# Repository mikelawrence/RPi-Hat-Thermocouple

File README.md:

# Raspberry Pi Thermocouple Hat
This is a [Raspberry Pi B+ Hat](https://github.com/raspberrypi/hats) PCB that supports:
* Three MAX31855 Thermocouple Converters for remote temperature sensing
* DS18S20 1-Wire Thermometer for local hat temperature
* DS3231M I2C Real Time Clock for keeping the time when Raspberry is not connected to the internet
* Magnetic Buzzer/Alert (Added with Rev 1.1)

PCB is designed in [KiCad](http://kicad.org) which is a great free EDA toolset and is based on [RPi_Hat_Template](https://github.com/xesscorp/RPi_Hat_Template) by XESS Corp.

## Status
* Rev 1.2 PCB  has been ordered from OSH Park but has NOT been tested yet.
  * Added R7 to prevent the Alert Buzzer from sounding when powered on.
  * Added Analog Power LDO Regulator to help with noise on the MAX31855's temperature readings. Not clear if this will help.
  * You can order parts from Mouser using this [shared BOM](http://www.mouser.com/ProjectManager/ProjectDetail.aspx?AccessID=20F70B46A4).
  * You can order the PCB from OSH Park using this [link](https://oshpark.com/shared_projects/3POTkoNz).
* Rev 1.1 PCB added an Alert Buzzer and has been ordered from OSH Park, assembled, and tested.
  * The Alert Buzzer sounds as soon as the board is powered. Adding a pulldown to base of NUD3124 fixes the problem.
  * There is occasional noise in the temperature readings from the MAX31855's.
* Rev 1.0 PCB has been ordered from OSH Park, assembled, and tested. It is fully operational.

## Board Preview

## Raspberry Pi Setup
This setup makes two key assumptions. First you are using Raspbian Jessie. Second Python3 is the target programming environment. Python3 should be installed by default but if it isn't run `sudo apt-get install python3-dev`.

### Configure ID EEPROM
Raspberry Pi Hats require an ID EEPROM with data that uniquely identifies every hat ever made. Start by cloning this repository on your Raspberry Pi, building the EEPROM tools, and make the the `eeprom_settings.eep` file.
```
cd ~/Documents
git clone https://github.com/mikelawrence/RPi-Hat-Thermocouple
cd ~/Documents/RPi-Hat-Thermocouple/eeprom/
make all
./eepmake eeprom_settings.txt eeprom_settings.eep
```
The next command writes the freshly generated and unique `eeprom_settings.eep` file to the EEPROM but you must push and hold the write switch on the hat before executing this command. By default the EEPROM on the hat is write protected. Pushing the write switch allows writes to occur while the switch is pushed.
```
sudo ./eepflash.sh -w -f=eeprom_settings.eep -t=24c32
```
You will see the following if writing to the EEPROM was successful.
```
This will attempt to talk to an eeprom at i2c address 0x50. Make sure there is an eeprom at this address.
This script comes with ABSOLUTELY no warranty. Continue only if you know what you are doing.
Do you wish to continue? (yes/no): yes
Writing...
0+1 records in
0+1 records out
117 bytes (117 B) copied, 2.31931 s, 0.1 kB/s
Done.
```
This is what you will see if there is a problem communicating with the EEPROM.
```
This will attempt to talk to an eeprom at i2c address 0x50. Make sure there is an eeprom at this address.
This script comes with ABSOLUTELY no warranty. Continue only if you know what you are doing.
Do you wish to continue? (yes/no): yes
Writing...
dd: error writing ‘/sys/class/i2c-adapter/i2c-3/3-0050/eeprom’: Connection timed out
0+1 records in
0+0 records out
0 bytes (0 B) copied, 0.0539977 s, 0.0 kB/s
Error doing I/O operation.
```
If you succesfuly wrote the EEPROM there is nothing else left to do here.

### Setup Interfaces
For this Hat you will need to enable the SPI, I2C and 1-Wire interfaces. From the command line type
`sudo raspi-config ` and follow the prompts to install SPI support in the kernel.

Now follow the same actions but enabling the I2C and 1-Wire interfaces.

It's time to reboot your Raspberry Pi with `sudo reboot`.

### Configuring the DS3231 RTC
Now let's see if the RTC is is present on the I2C bus by running `sudo i2cdetect -y 1`. If you get a `command not found` you will need to install it with `sudo apt-get install python-smbus i2c-tools`. Looking at the output of the `i2cdetect` command you will see `68` in a field of `--` when the RTC is detected on the bus.
```
pi@raspberrypi:~ $ sudo i2cdetect -y 1
     0  1  2  3  4  5  6  7  8  9  a  b  c  d  e  f
00:          -- -- -- -- -- -- -- -- -- -- -- -- --
10: -- -- -- -- -- -- -- -- -- -- -- -- -- -- -- --
20: -- -- -- -- -- -- -- -- -- -- -- -- -- -- -- --
30: -- -- -- -- -- -- -- -- -- -- -- -- -- -- -- --
40: -- -- -- -- -- -- -- -- -- -- -- -- -- -- -- --
50: -- -- -- -- -- -- -- -- -- -- -- -- -- -- -- --
60: -- -- -- -- -- -- -- -- 68 -- -- -- -- -- -- --
70: -- -- -- -- -- -- -- --                         
```
Enable kernel support for the DS3231 RTC by adding a device tree overlay by running `sudo nano /boot/config.txt` and adding the following to the end of the file. Don't forget to save the file.
```
# Enable Real Time Clock
dtoverlay=i2c-rtc,ds3231
```
Reboot again. Now when `sudo i2cdetect -y 1` is run we see:
```
pi@raspberrypi:~ $ sudo i2cdetect -y 1
     0  1  2  3  4  5  6  7  8  9  a  b  c  d  e  f
00:          -- -- -- -- -- -- -- -- -- -- -- -- --
10: -- -- -- -- -- -- -- -- -- -- -- -- -- -- -- --
20: -- -- -- -- -- -- -- -- -- -- -- -- -- -- -- --
30: -- -- -- -- -- -- -- -- -- -- -- -- -- -- -- --
40: -- -- -- -- -- -- -- -- -- -- -- -- -- -- -- --
50: -- -- -- -- -- -- -- -- -- -- -- -- -- -- -- --
60: -- -- -- -- -- -- -- -- UU -- -- -- -- -- -- --
70: -- -- -- -- -- -- -- --                         
```
The `UU` at address 68 means the RTC is currently in use by a driver or in other words we have success! Now disable the fake hwclock because it will interfere with our new RTC. Issue the following commands.
```
sudo apt-get -y remove fake-hwclock
sudo update-rc.d -f fake-hwclock remove
```
Next run `sudo nano /lib/udev/hwclock-set` and comment out the following lines. This puts the original clock script back to normal.
```
#if [ -e /run/systemd/system ] ; then
# exit 0
#fi
```
### Setting the time in the RTC
First make sure you have installed the CR1225 battery on the Hat. Next verify the Raspberry Pi has the correct time by typing `date`.
```
pi@raspberrypi:~ $ date
Fri Mar 10 16:52:48 CST 2017
```
If the time is not correct connect the Raspberry Pi to a network via Ethernet or WiFi and allow it synchronize with Internet time servers or set the time manually. Once the time is correct issue this command `sudo hwclock -w`. This will set the RTC time to current system time. The next time the Raspberry Pi is booted it will get it's time from the RTC.

### Using the DS18S20 1-Wire Thermometer
[Here](https://github.com/timofurrer/w1thermsensor) is a nice 1-Wire python library that also supports command line reading of the temperature. If you get a 'command not found' then install it with `sudo apt-get install python3-w1thermsensor`.

Now test the Thermocouple Hat's DS18S20 temperature sensor with `pi@raspberrypi:~ $`.
```
pi@raspberrypi:~ $ w1thermsensor all
Got temperatures of 1 sensors:
  Sensor 1 (0008033f727f) measured temperature: 32.312 celsius
```
### Using the MAX31855 SPI Thermocouple Converters
The Thermocouple Hat design gets around the Raspberry Pi limitation of only two chip enables for the hardware SPI0 interface by adding a 74LVC139A 2to4 Decoder to CEO. The address lines of the 2to4 decoder are connected to GPIO24 and GPIO23 so when SPI0.CE0 is sent low only one of the Thermocouple converters will be selected according to the following logic.

| GPIO23 (Pin 16) | GPIO24 (Pin 18) | Thermocouple |
|:---------------:|:---------------:|--------------|
|        0        |        0        | TC1          |
|        0        |        1        | TC2          |
|        1        |        0        | TC3          |
|        1        |        1        | Invalid      |

[Spidev](https://github.com/doceme/py-spidev) is a commonly used Python library for Raspberry Pi SPI programming. This library is most likely already installed but if not install it with `sudo apt-get install python3-spidev`. Assuming you already cloned this repository issue this command `~/Documents/RPi-Hat-Thermocouple/code/test.py` to see the DS18S20 PCB and thermocouple temperatures. Note when I ran the test on my board there was only one connected thermocouple so the other MAX31855K's show as 'No thermocouple connected'.
```
pi@raspberrypi:~ $ ~/Documents/RPi-Hat-Thermocouple/code/test.py
Press Ctrl-C to quit.
Testing alert buzzer...

DS18S20 on PCB: 28.88C / 83.97F
Thermocouple 0: 21.63C / 70.93F
Thermocouple 1: Error - No thermocouple connected
Thermocouple 2: Error - No thermocouple connected
```
# Acknowledgments
[Adafruit](www.adafruit.com) released a guide to [configuring a RTC on a Raspberry Pi](https://cdn-learn.adafruit.com/downloads/pdf/adding-a-real-time-clock-to-raspberry-pi.pdf) that was extremely helpful is setting up the DS3231M RTC. The MAX31855 code is based on an Adafruit [library](https://github.com/adafruit/Adafruit_Python_MAX31855).

Adafruit has breakout boards for the key chips on this Hat here: [RTC](https://www.adafruit.com/products/3013) and [MAX31855](https://www.adafruit.com/products/269). They support the open soruce/hardware community so support them.

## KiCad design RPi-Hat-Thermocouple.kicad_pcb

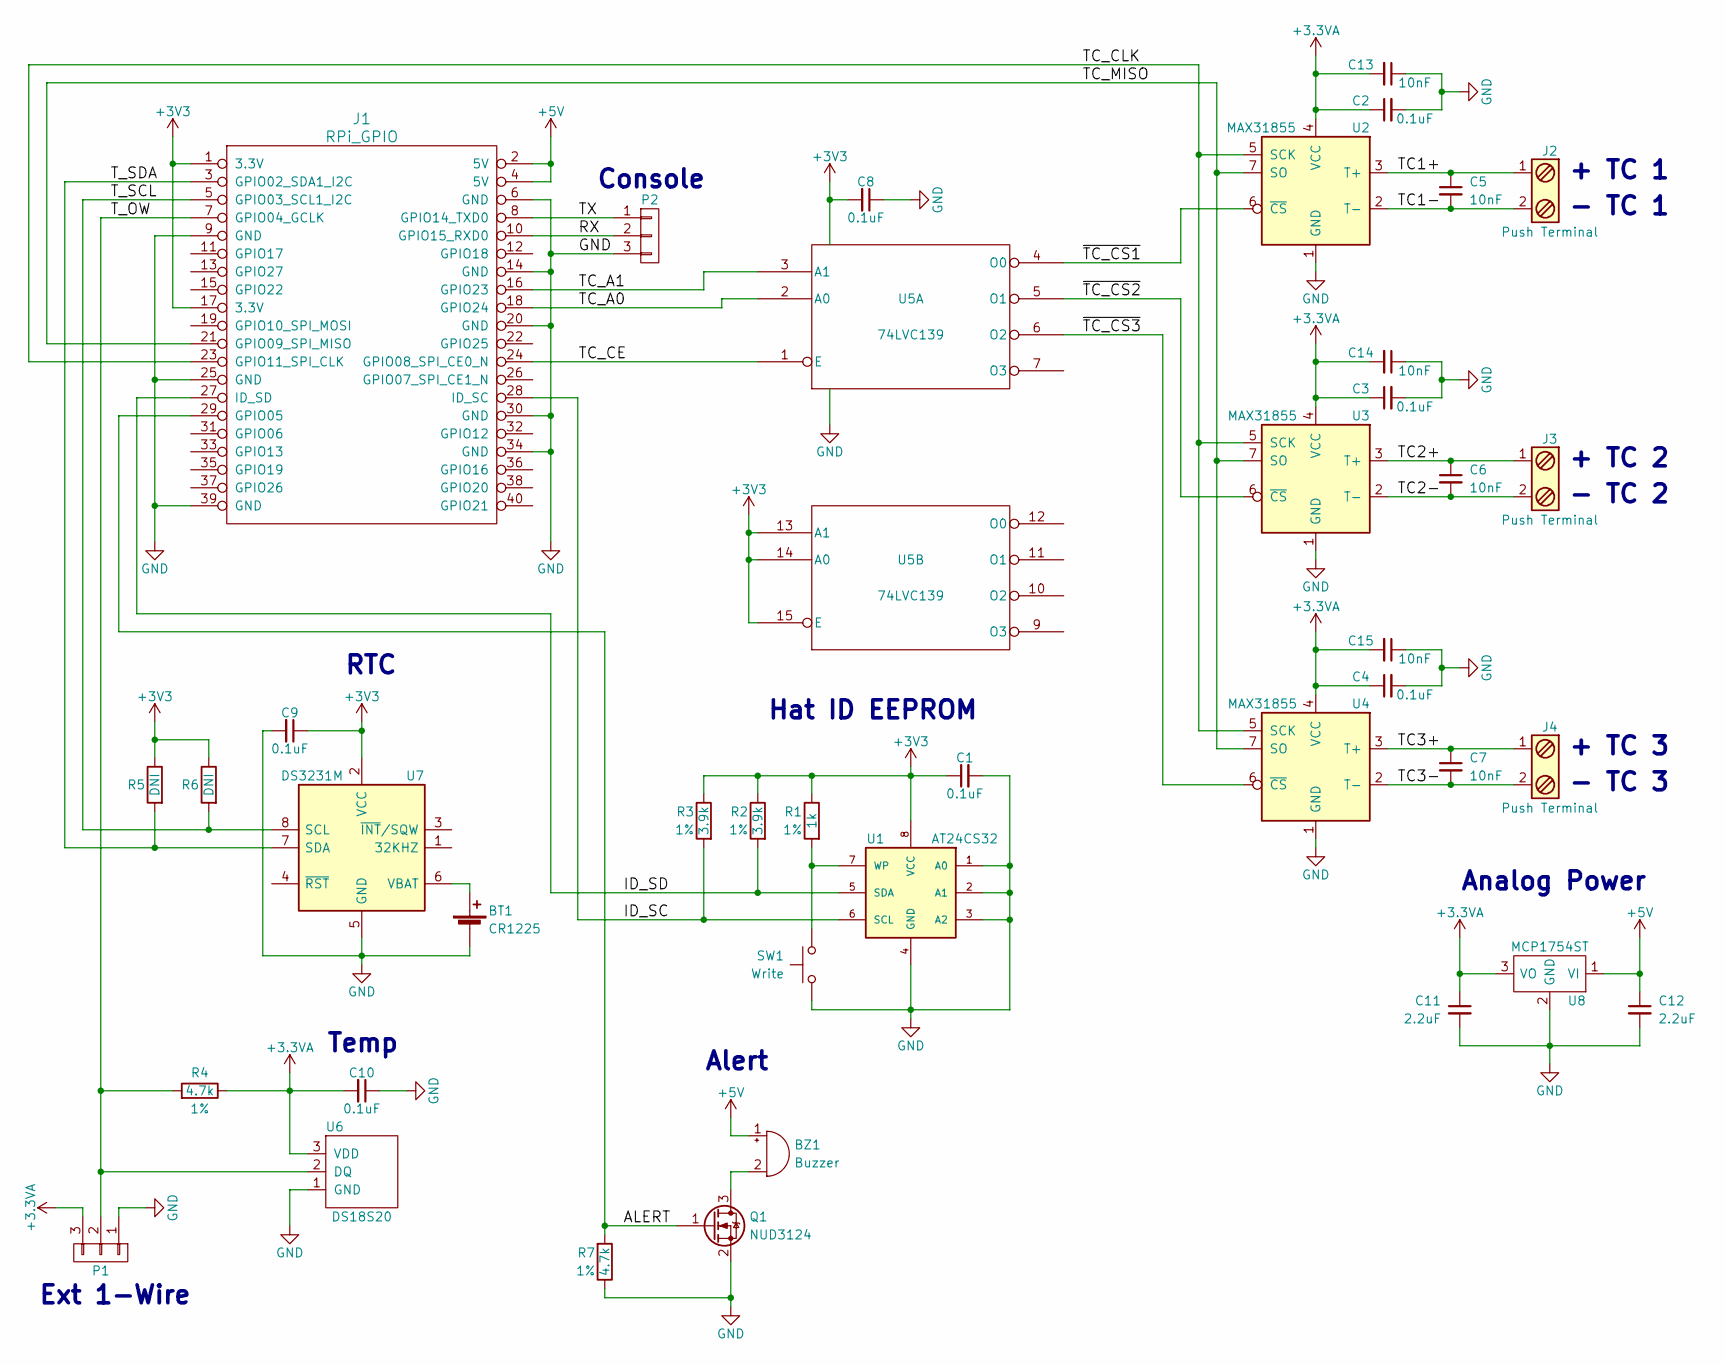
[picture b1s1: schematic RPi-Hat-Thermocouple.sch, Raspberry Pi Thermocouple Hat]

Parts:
BT1: CR1225; Keystone_3000_1x12mm-CoinCell; Part Number 3000
BZ1: Buzzer; CMI-9655S-SMT; Part Number CMI-9655S-SMT-TR
C1, C2, C3, C4, C8, C9, C10: 0.1uF; C_0603; Part Number GRM188R71H104KA93D
C5, C6, C7, C13, C14, C15: 10nF; C_0603; Part Number GRM188R71H103KA01D
C11, C12: 2.2uF; C_0805; Part Number GRM21BR71C225KA12L
J1: RPi_GPIO; Pin_Header_Straight_2x20; Part Number 2222
J2, J3, J4: Push Terminal; PhoenixContact_PTSM0,5_2-2,5-V_SMD; Part Number 1771091
P1: CONN_01X03; Pin_Header_Straight_1x03_Pitch2.00mm
P2: CONN_01X03; Pin_Header_Straight_1x03_Pitch2.54mm
Q1: NUD3124; SOT-23; Part Number NUD3124LT1G
R1: 1k; R_0603; Tolerance 1%; Part Number ERJ-3EKF1001V
R2, R3: 3.9k; R_0603; Tolerance 1%; Part Number ERJ-3EKF3901V
R4, R7: 4.7k; R_0603; Tolerance 1%; Part Number ERJ-3EKF4701V
R5, R6: DNI; R_0603
SW1: Write; SW_SPST_B3U-1000P-B; Part Number B3U-1000P
U1: AT24CS32; SOIC-8_3.9x4.9mm_Pitch1.27mm; Part Number AT24CS32-SSHM
U2, U3, U4: MAX31855; SOIC-8_3.9x4.9mm_Pitch1.27mm; Part Number MAX31855KASA+
U5: 74LVC139; TSSOP-16_4.4x5mm_Pitch0.65mm; Part Number SN74LVC139APWR
U6: DS18S20; TO-92_Molded_Narrow; Part Number DS18S20
U7: DS3231M; SOIC-8_3.9x4.9mm_Pitch1.27mm; Part Number DS3231MZ
U8: MCP1754ST; SOT89-3_Housing; Part Number MCP1754ST-3302E/MB

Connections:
+3.3VA: C2.1, C3.1, C4.1, C10.2, C11.1, C13.2, C14.2, C15.2, P1.3, R4.1, U2.4 (VCC), U3.4 (VCC), U4.4 (VCC), U6.3 (VDD), U8.3 (VO)
+3V3: C1.1, C8.2, C9.1, J1.1 (3.3V), J1.17 (3.3V), R1.1, R2.1, R3.1, R5.1, R6.1, U1.8 (VCC), U5.13 (A1), U5.14 (A0), U5.15 (E), U5.16 (VCC), U7.2 (VCC)
+5V: BZ1.1 (-), C12.1, J1.2 (5V), J1.4 (5V), U8.1 (VI)
/ALERT: J1.29 (GPIO05), Q1.1 (G), R7.2
/ID_SC: J1.28 (ID_SC), R3.2, U1.6 (SCL)
/ID_SD: J1.27 (ID_SD), R2.2, U1.5 (SDA)
/RX: J1.10 (GPIO15_RXD0), P2.2
/TC1+: C5.1, J2.1, U2.3 (T+)
/TC1-: C5.2, J2.2, U2.2 (T-)
/TC2+: C6.1, J3.1, U3.3 (T+)
/TC2-: C6.2, J3.2, U3.2 (T-)
/TC3+: C7.1, J4.1, U4.3 (T+)
/TC3-: C7.2, J4.2, U4.2 (T-)
/TC_A0: J1.18 (GPIO24), U5.2 (A0)
/TC_A1: J1.16 (GPIO23), U5.3 (A1)
/TC_CE: J1.24 (GPIO08_SPI_CE0_N), U5.1 (E)
/TC_CLK: J1.23 (GPIO11_SPI_CLK), U2.5 (SCK), U3.5 (SCK), U4.5 (SCK)
/TC_MISO: J1.21 (GPIO09_SPI_MISO), U2.7 (SO), U3.7 (SO), U4.7 (SO)
/TX: J1.8 (GPIO14_TXD0), P2.1
/T_OW: J1.7 (GPIO04_GCLK), P1.2, R4.2, U6.2 (DQ)
/T_SCL: J1.5 (GPIO03_SCL1_I2C), R6.2, U7.8 (SCL)
/T_SDA: J1.3 (GPIO02_SDA1_I2C), R5.2, U7.7 (SDA)
/~TC_CS1~: U2.6 (~CS~), U5.4 (O0)
/~TC_CS2~: U3.6 (~CS~), U5.5 (O1)
/~TC_CS3~: U4.6 (~CS~), U5.6 (O2)
GND: BT1.2 (-), C1.2, C2.2, C3.2, C4.2, C8.1, C9.2, C10.1, C11.2, C12.2, C13.1, C14.1, C15.1, J1.6 (GND), J1.9 (GND), J1.14 (GND), J1.20 (GND), J1.25 (GND), J1.30 (GND), J1.34 (GND), J1.39 (GND), P1.1, P2.3, Q1.2 (S), R7.1, SW1.2, U1.1 (A0), U1.2 (A1), U1.3 (A2), U1.4 (GND), U2.1 (GND), U3.1 (GND), U4.1 (GND), U5.8 (GND), U6.1 (GND), U7.5 (GND), U8.2 (GND)
unnamed: BT1.1 (+), U7.6 (VBAT)
unnamed: BZ1.2 (+), Q1.3 (D)
unnamed: R1.2, SW1.1, U1.7 (WP)

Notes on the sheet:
+ TC 1
- TC 1
Hat ID EEPROM
RTC
Temp
Alert
Ext 1-Wire
Console
Analog Power
+ TC 3
- TC 3
+ TC 2
- TC 2

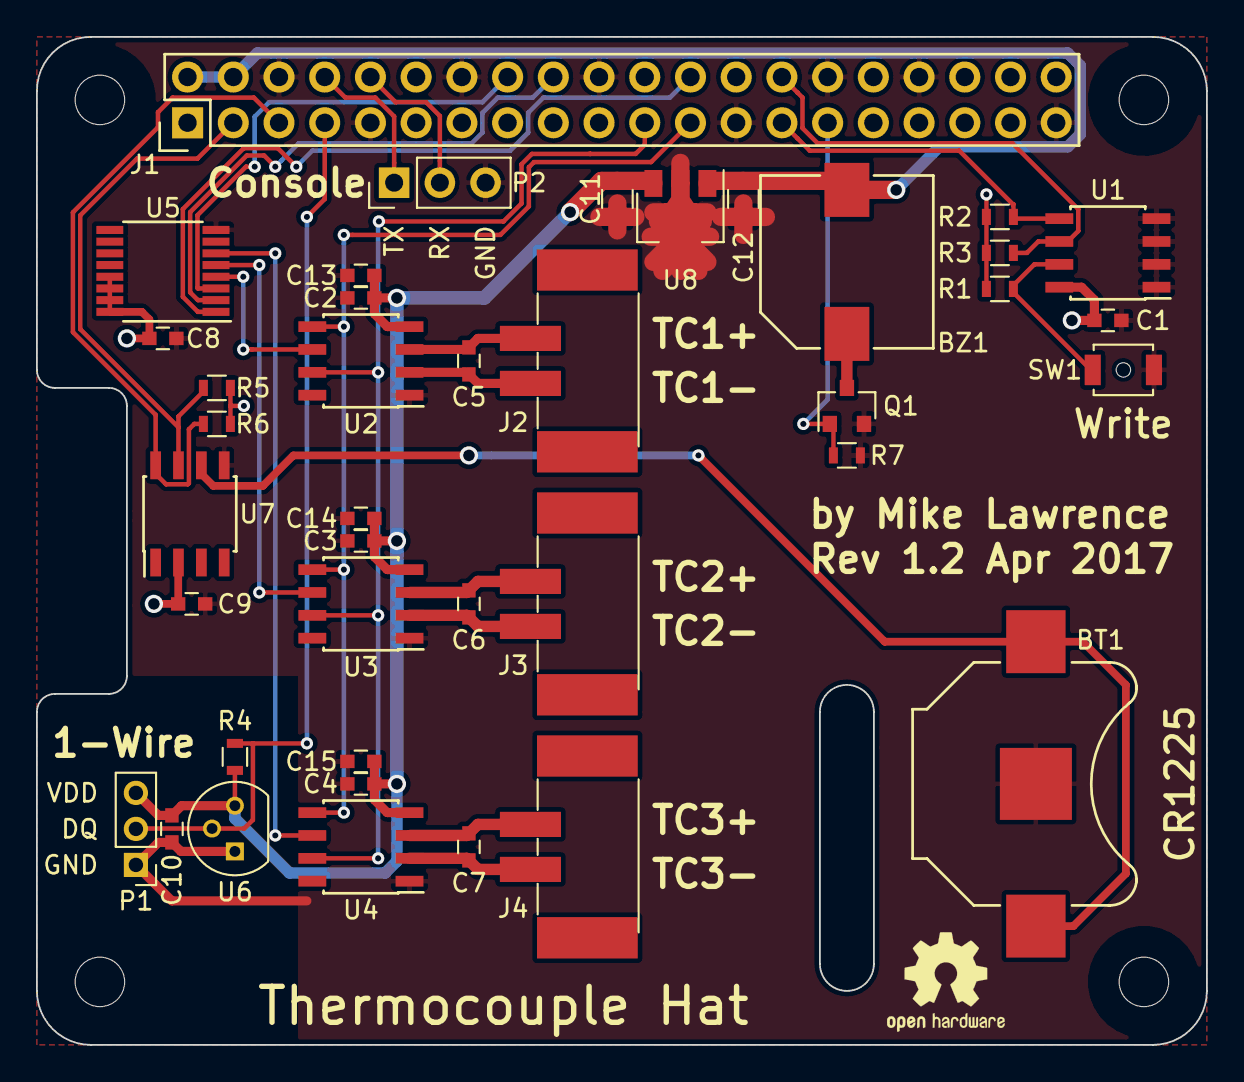
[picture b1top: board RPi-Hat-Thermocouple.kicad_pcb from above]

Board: 2 copper layers, 65.0 x 56.0 mm, 40 parts (0 on the bottom side), 29 nets.

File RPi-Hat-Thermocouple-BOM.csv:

Qty,Reference, Value, Part Number, Manufacturer, Footprint, Vendor, Vendor Part Number, Tolerance
3,J2-J4,Push Terminal,1771091,Phoenix Contact,"Connectors_Phoenix:PhoenixContact_PTSM0,5_2-2,5-V_SMD",Mouser,651-1771091,
1,U1,AT24CS32,AT24CS32-SSHM,Atmel,Housings_SOIC:SOIC-8_3.9x4.9mm_Pitch1.27mm,Mouser,556-AT24CS32-SSHM-T,
1,U6,DS18S20,DS18S20,Maxim Integrated,TO_SOT_Packages_THT:TO-92_Molded_Narrow,Mouser,700-DS18S20,
1,U7,DS3231M,DS3231MZ,Maxim Integrated,Housings_SOIC:SOIC-8_3.9x4.9mm_Pitch1.27mm,Mouser,700-DS3231MZ+,
1,R1,1k,ERJ-3EKF1001V,Panasonic,Resistors_SMD:R_0603,Mouser,667-ERJ-3EKF1001V,1%
2,R2-R3,3.9k,ERJ-3EKF3901V,Panasonic,Resistors_SMD:R_0603,Mouser,667-ERJ-3EKF3901V,1%
1,R4-R7,4.7k,ERJ-3EKF4701V,Panasonic,Resistors_SMD:R_0603,Mouser,667-ERJ-3EKF4701V,1%
6,C5-C7 C13-C15,10nF,GRM188R71H103KA01D,Murata Electronics,Capacitors_SMD:C_0603,Mouser,81-GRM39X103K50D,
7,C1-C4 C8-C9 C10,0.1uF,GRM188R71H104KA93D,Murata Electronics,Capacitors_SMD:C_0603,Mouser,81-GRM39X104K50D,
2,C11-C12,2.2uF,GRM21BR71C225KA12L,Murata Electronics,Mouser,81-GRM21BR71C225KA2L,
3,U2-U4,MAX31855,MAX31855KASA+,Maxim Integrated,Housings_SOIC:SOIC-8_3.9x4.9mm_Pitch1.27mm,Mouser,700-MAX31855KASA+,
1,U5,74LVC139,SN74LVC139APWR,TI,Housings_SSOP:TSSOP-16_4.4x5mm_Pitch0.65mm,Mouser,595-SN74LVC139APWR,
1,J1,RPi_GPIO,2222,Adafruit,raspberry-ml:Pin_Header_Straight_2x20,Mouser,485-2222,
1,SW1,Write,B3U-1000P,Omron,Buttons_Switches_SMD:SW_SPST_B3U-1000P-B,Mouser,653-B3U-1000P,
1,BT1,CR1225,3000,Keystone Electronics,Battery_Holders:Keystone_3000_1x12mm-CoinCell,Mouser,534-3000,
1,BZ1,Buzzer,CUI,CMI-9655S-SMT-TR,cui-ml:CMI-9655S-SMT,Mouser,490-CMI-9655S-SMT-TR,
1,Q1,NUD3124,OnSemi,NUD3124LT1G,TO_SOT_Packages_SMD:SOT-23,Mouser,863-NUD3124LT1G,
1,U8,MCP1754ST,MCP1754ST-3302E/MB,Microchip,Mouser,579-MCP1754ST3302EMB,

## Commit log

2017-02-26 Small edit to README file. Added missing data sheet.
2017-03-02 Added BOM section to readme file.
2017-03-03 Cleanup Fab layers. Add board preview.
2017-03-07 Updated READMEs. Added eeprom and code directories.
2017-03-08 Added some exception handling.
2017-03-08 Improve readme.
2017-03-10 Finished README
2017-03-10 Fixed a couple of mistakes in the README
2017-03-10 Added thermocouple error handling
2017-03-11 README corrections
2017-03-12 Added Alert Buzzer.
    Rev 1.1 will be released soon.
2017-03-21 Updated EEPROM settings alert is pulled low
2017-03-22 Code now tests alert signal
2017-03-22 Add R7
    R7 prevents alert from going off until software
2017-03-22 Minor README correction
2017-03-24 Few updates to the Status section of the Readme file
2017-04-08 Added Analog Power LDO regulator
2021-11-08 Update Kicad link.
